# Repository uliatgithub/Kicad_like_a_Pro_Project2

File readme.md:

Project 2 - RPI FS HAT by Peter Dalmaris

My version of the Raspberry PI HAT Project. This project is based on the "Kicad like a Pro" book written by Dr. Peter Dalmaris.
I made some modifications:
	- using a 2x08 header socket
	- a different footpring of the push button
	- own silk screen layout

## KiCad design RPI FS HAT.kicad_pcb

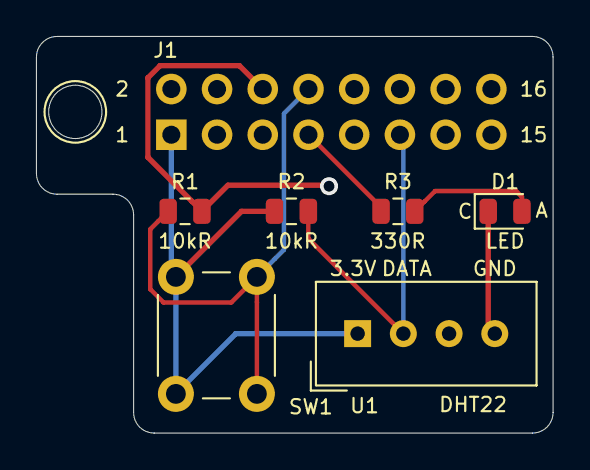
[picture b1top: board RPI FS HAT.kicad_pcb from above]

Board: 2 copper layers, 28.7 x 22.0 mm, 7 parts (1 on the bottom side), 6 nets.

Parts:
D1: LED; LED_0805_2012Metric
J1: Raspberry_Pi_2_3; PinSocket_2x08_P2.54mm_Vertical
R1, R2: 10kR; R_0805_2012Metric
R3: 330R; R_0805_2012Metric
SW1: SW_DPST; SW_PUSH_6mm
U1: DHT22; Aosong_DHT11_5.5x12.0_P2.54mm

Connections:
/3.3V: J1.1, R2.1, SW1.1, U1.1
/button_input: J1.8, R1.1, SW1.2
/sensor_data: J1.11, R2.2, U1.2
GND: D1.1, J1.6, J1.9, R1.2, U1.4
unnamed: D1.2, R3.2
unnamed: J1.7, R3.1

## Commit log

2019-04-29 final first version
2019-04-29 readme.md added for remote repository push
2019-04-29 license file created
